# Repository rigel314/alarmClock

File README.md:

alarmClock
========
# About
My fiancé wanted an alarm clock that simulated a sunrise before ringing.  Since all the ones you can buy are expensive, dumb, or both, I decided to make one.

# Dependencies
 * [My fork of firelizzard's Nokia LCD library](https://github.com/rigel314/Arduino-LCD-Screen), which is a submodule
  * This should be installed as a normal Arduino library. For me, this was:
    * `git submodule update --init`
    * `cp -a Arduino-LCD-Screen ../../libraries/`
 * [TimerOne](https://github.com/PaulStoffregen/TimerOne) as installed by the teensy installer or the Arduino IDE "Manage Libraries" interface
 * [Time](https://github.com/PaulStoffregen/Time) as installed by the teensy installer or the Arduino IDE "Manage Libraries" interface
 * [DS1307RTC](https://github.com/PaulStoffregen/DS1307RTC) as installed through the Arduino IDE "Manage Libraries" interface

# Hardware
 * 3-color LED strip
 * Resistors and transistors
 * DS1307 Real Time Clock
 * MCP4725 I2C DAC for audio
 * Speaker
 * Nokia 5110 84x48 pixel LCD screen
 * Arduino Duemilanove/Uno with atmega328P
 * 12V power supply

See the [/eagle](https://github.com/rigel314/alarmClock/tree/master/eagle) folder in this repo for the board layout.

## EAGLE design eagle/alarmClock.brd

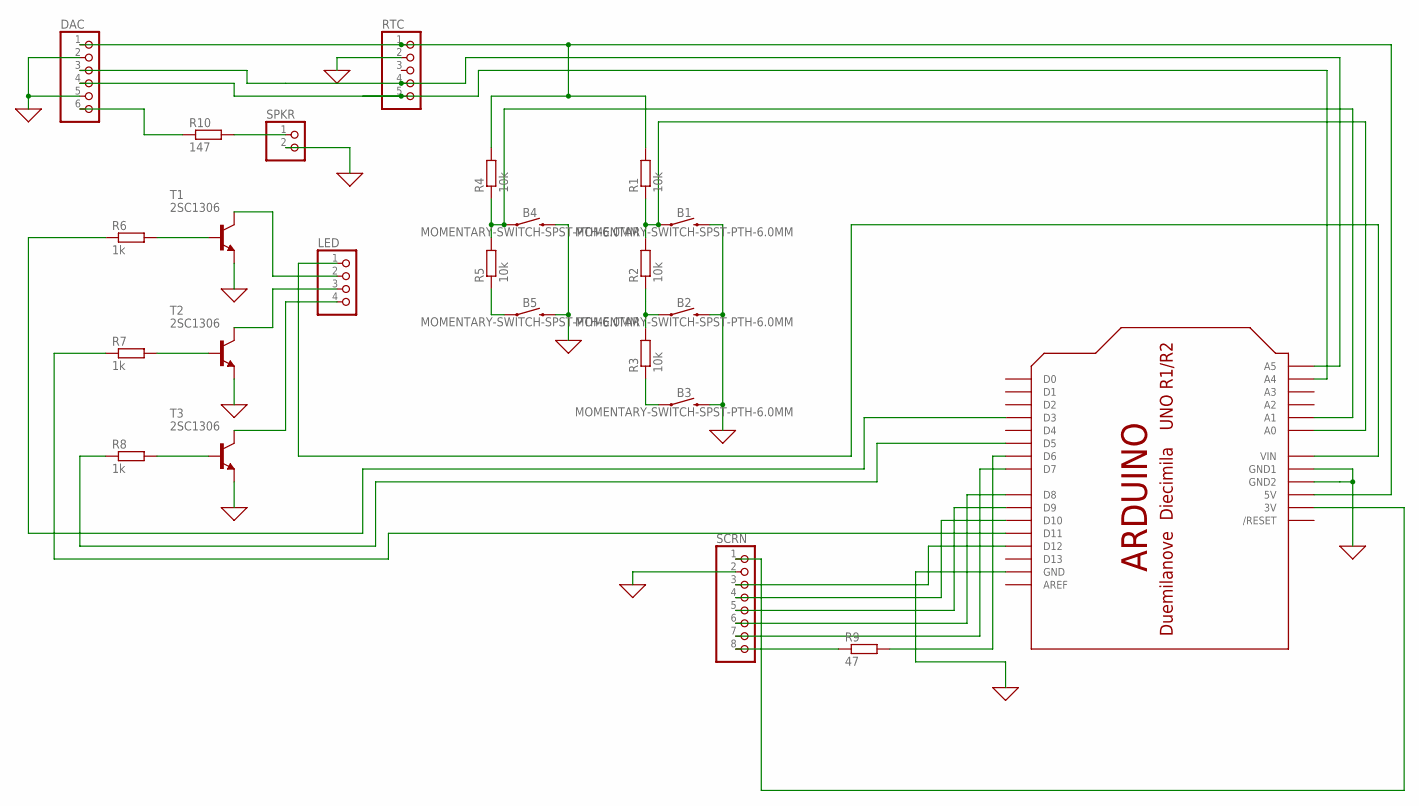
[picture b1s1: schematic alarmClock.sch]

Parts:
B1, B2, B3, B4, B5: MOMENTARY-SWITCH-SPST-PTH-6.0MM; TACTILE_SWITCH_PTH_6.0MM
DAC: PINHD-1X6; 1X06
LED: PINHD-1X4; 1X04
R1, R2, R3, R4, R5: 10k; 0204/7
R6, R7, R8: 1k; 0204/7
R9: 47; 0204/7
R10: 147; 0204/7
RTC: PINHD-1X5; 1X05
SCRN: PINHD-1X8; 1X08
SPKR: PINHD-1X2; 1X02
T1, T2, T3: 2SC1306; TO220BV
U$1: ARDUINOUNO; ARDUINO

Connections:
0: B1.3 (2), B2.3 (2), B3.3 (2), B4.3 (2), B5.3 (2), DAC.2, DAC.5, RTC.2, SCRN.2, SPKR.2, T1.3 (E), T2.3 (E), T3.3 (E), U$1.GND, U$1.GND1, U$1.GND2
unnamed: B1.1, R1.1, R2.2, U$1.A0
unnamed: B3.1, R3.1
unnamed: B2.1, R2.1, R3.2
unnamed: B5.1, R5.1
unnamed: B4.1, R4.1, R5.2, U$1.A1
unnamed: R6.2, T1.1 (B)
unnamed: R8.2, T3.1 (B)
unnamed: R7.2, T2.1 (B)
unnamed: DAC.4, RTC.5, U$1.A4
unnamed: DAC.3, RTC.4, U$1.A5
unnamed: DAC.1, R1.2, R4.2, RTC.1, U$1.5V
unnamed: DAC.6, R10.1
unnamed: LED.1, U$1.VIN
unnamed: LED.2, T1.2 (C)
unnamed: LED.4, T3.2 (C)
unnamed: LED.3, T2.2 (C)
unnamed: R6.1, U$1.D3
unnamed: R8.1, U$1.D5
unnamed: SCRN.7, U$1.D7
unnamed: R9.2, U$1.D6
unnamed: SCRN.6, U$1.D8
unnamed: R7.1, U$1.D11
unnamed: SCRN.5, U$1.D9
unnamed: SCRN.4, U$1.D10
unnamed: SCRN.3, U$1.D12
unnamed: SCRN.1, U$1.3V
unnamed: R9.1, SCRN.8
unnamed: R10.2, SPKR.1

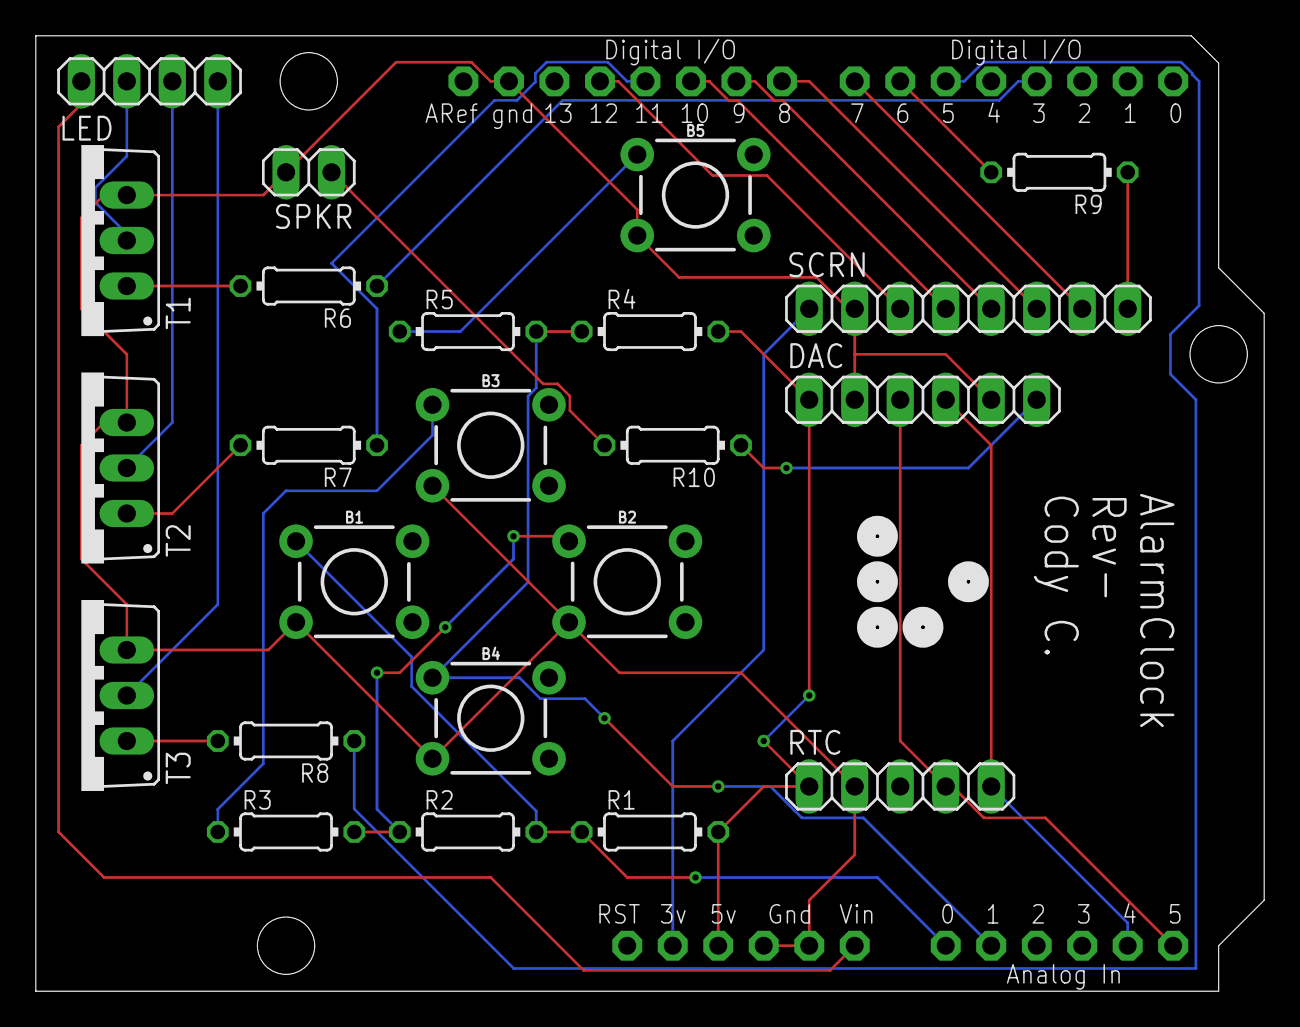
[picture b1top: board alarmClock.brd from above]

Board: 2 copper layers, 68.6 x 53.3 mm, 24 parts (0 on the bottom side), 29 nets.

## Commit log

2017-12-22 Initial test including Ethan's Nokia screen library.
2017-12-22 Add readme
2017-12-22 Add license
2017-12-23 Fix partnumbers
2017-12-23 Add LED strip and Screen commanding
2017-12-23 sane buttons
2017-12-23 Add time library example
2017-12-24 Setup time sync from RTC, but use now() for getting actual time.
2017-12-24 Add Eagle project
2017-12-25 Add bird noise PoC
2017-12-25 Update Rev- for sending to fab
2017-12-25 Add comment
2017-12-26 Detect long press, split code into multiple files
2017-12-26 Add simple mode handling with a demo mode.
2017-12-26 Initialize screen message
2017-12-26 Add concept of unhandled buttons and default actions.
2017-12-26 Fix needing to mask off high bits during audio play by casting pgm_read_byte to signed int8.
2017-12-26 Add button repeat.
2017-12-26 Inline modeMux function
2017-12-28 Add time set mode
2017-12-31 Add schematic
2017-12-31 Add submodule for screen library.
2017-12-31 add link in readme
2017-12-31 fix url in readme
2017-12-31 fix readme
2017-12-31 Add submodule instructions to readme
2017-12-31 Weird bug
2017-12-31 Fix buffer overflow
2017-12-31 Change to u8 for alarm settings
2017-12-31 Pass varargs to serial.println
2017-12-31 Formatting, and some extra logs
2017-12-31 Completed set alarm mode
2018-01-03 fix indents in readme
2018-01-08 Add alarm handling
2018-01-19 Add debug
2018-02-04 Attempt to add submodes to normal mode
2018-02-05 Add normal mode's submode flow shown in Mode graphs.nb
2018-02-06 Add prev rgb signals
2018-02-06 Remove ambiance time from total alarm time, making sunrise start 30min before alarm time
2018-03-22 Use defines for max values per color
2018-03-22 Add persistent alarm storage.
2018-03-22 Revamp longpress/repeat detection
2018-03-26 Add alarm sound and ambiance sonuds and fix long press bugs.
2018-03-26 Fix alarm noise

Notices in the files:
parts and their libraries:
SparkFun-Switches: Licensing: Creative Commons ShareAlike 4.0 International - https://creativecommons.org/licenses/by-sa/4.0
